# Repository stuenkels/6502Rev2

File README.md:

# 6502v2 Computer Build

Please note while this design is based on Ben Eaters 6502 (eater.net/6502) computer, it is not 100% compatible. This is mostly due to the memory map being changed to make space for 3 interface chips, 2 c22s and a c51. 

Memory Map:
  0x0000 -> 0x3FFF : RAM
  0x4010 : Start of memory for the "GPIO" VIA
  0x4020 : Start of memory for the "LCD" VIA
  0x4040 : Start of memory for the Serial interface
  0x8000 -> 0xFFFF : ROM

It is very simple to refactor any code written for the BE6502 to work with this design, all you have to do is change the definitions for the different ports, ex PORTB = $6020 would be PORTB = $4020.  

# Pictures

<br>
The LCD header was mirrored on this first run of boards, the GERBER files and KiCad project have been updated in the repo.

If you want to build this PCB yourself, you can download the gerber.zip file and order it from JLCPCB or PCBWAY
MAKE SURE TO USE A FEMALE DB9 CONNECTOR FOR THE SERIAL PORT!!! The connecture in the picture is a male connector, and it does not work because the pins are in the wrong spots!

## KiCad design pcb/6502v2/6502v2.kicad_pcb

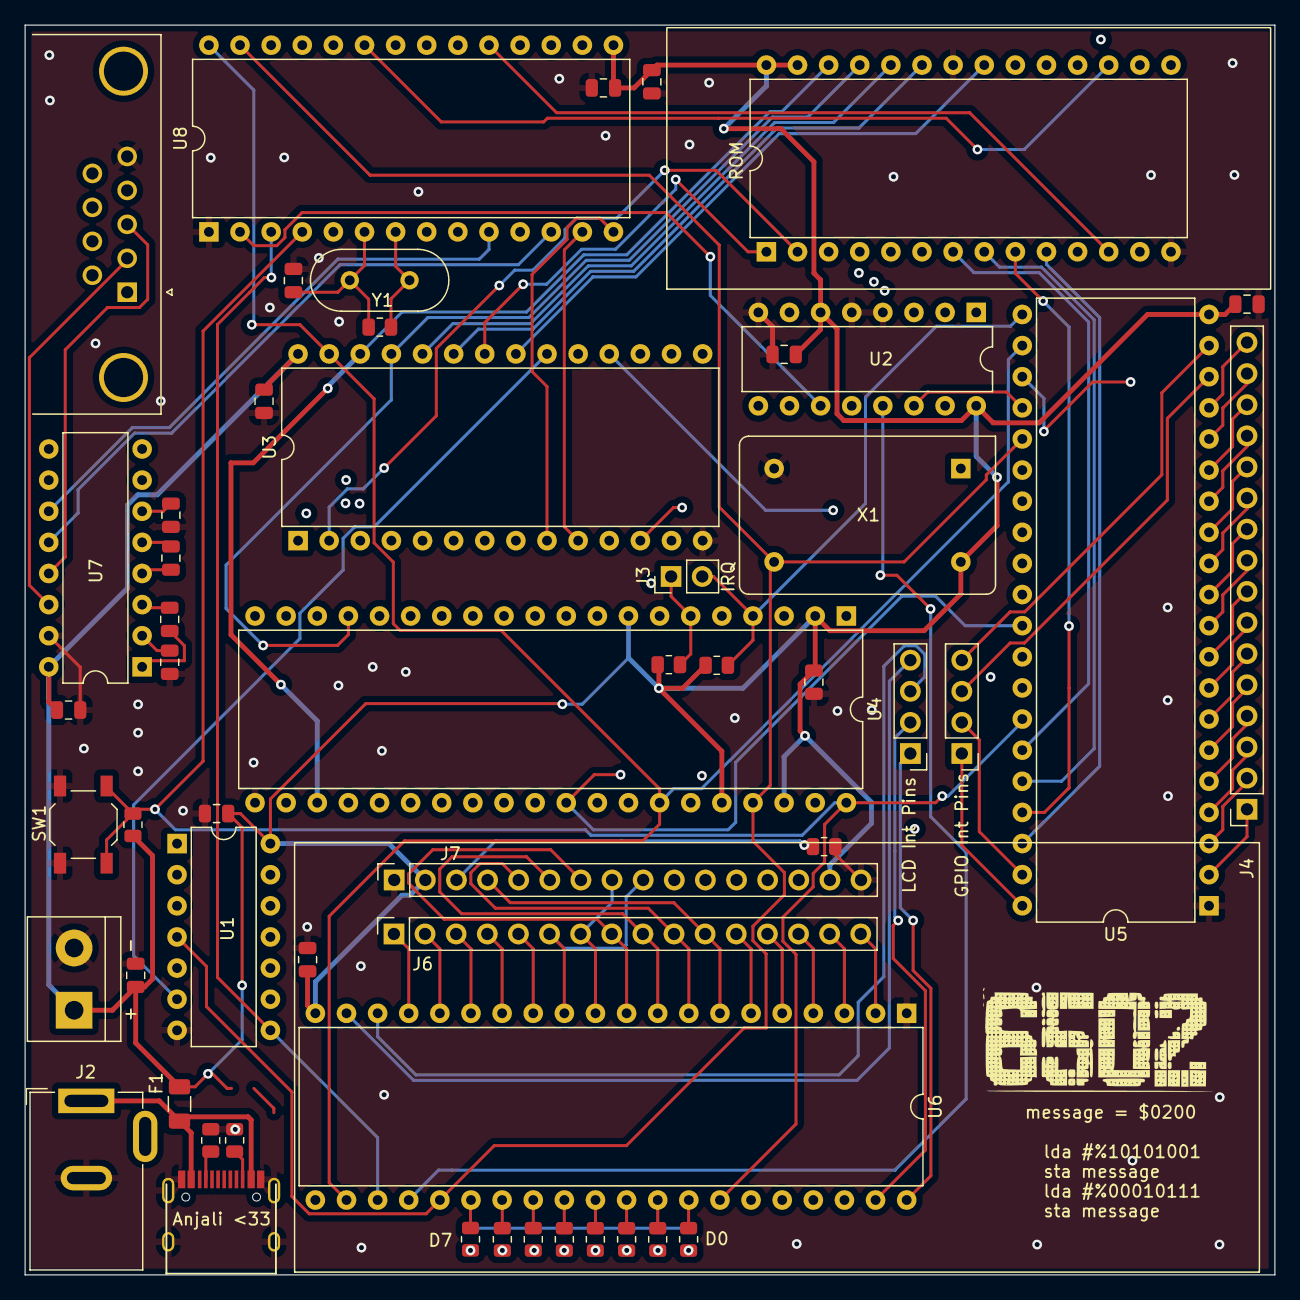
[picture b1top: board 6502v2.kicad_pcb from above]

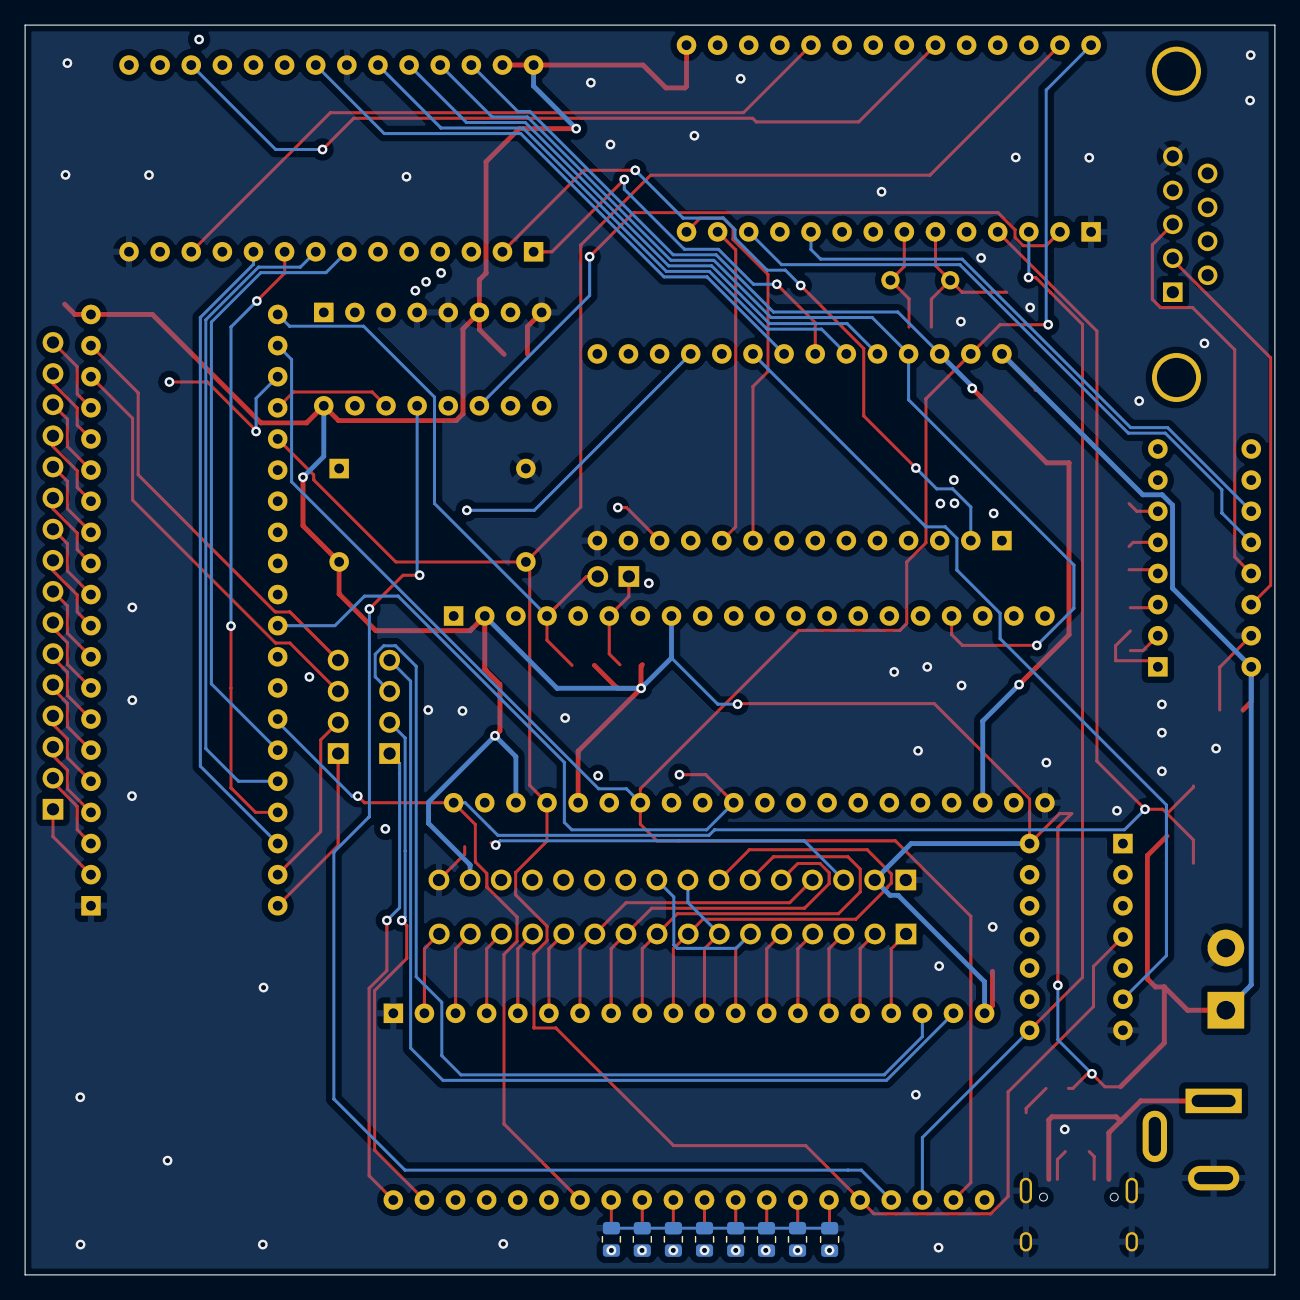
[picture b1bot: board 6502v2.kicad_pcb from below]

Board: 4 copper layers, 102.0 x 102.0 mm, 61 parts (8 on the bottom side), 101 nets.

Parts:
C1, C2, C3, C4, C5, C6, C7, C8, C9, C10: 10uF; C_0805_2012Metric
C11, C12, C13, C14: 1µF; C_0805_2012Metric
C15: 30 pF; C_0805_2012Metric
D2, D4, D6, D8, D10, D12, D14, D16: Blu; R_0805_2012Metric
F1: Polyfuse_Small; Fuse_1206_3216Metric
J1: Power; TerminalBlock_bornier-2_P5.08mm
J2: Barrel_Jack; BarrelJack_GCT_DCJ200-10-A_Horizontal
J3: Conn_01x02; PinHeader_1x02_P2.54mm_Vertical
J4, J6: I/O; PinSocket_1x16_P2.54mm_Vertical
J5, J8: Interup Pins; PinHeader_1x04_P2.54mm_Vertical
J7: LDC; PinSocket_1x16_P2.54mm_Vertical
J9: DB9_Female; DSUB-9_Female_Horizontal_P2.77x2.84mm_EdgePinOffset4.94mm_H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
R1, R2: 5.1k; R_0805_2012Metric
R4, R6, R8, R10, R12, R14, R16, R18, R29, R30: 220; R_0805_2012Metric
R31: 1k; R_0805_2012Metric
R32: R_Small; R_0805_2012Metric
R33: 1M; R_0805_2012Metric
SW1: SW_Push; SW_SPST_TL3342
U1: 74HC00; DIP-14_W7.62mm
U2: 74HC238; DIP-16_W7.62mm
U3: CY62256-70PC; DIP-28_W15.24mm
U4: W65C02SxP; DIP-40_W15.24mm
U5, U6: W65C22NxP; DIP-40_W15.24mm
U7: MAX232; DIP-16_W7.62mm
U8: W65C51NxP; DIP-28_W15.24mm
U9: 28C256; DIP-28_W15.24mm
USB1: HRO-TYPE-C-31-M-12
X1: DGOF5S3; Oscillator_DIP-14
Y1: 1.8432 Mh; Crystal_HC49-U_Vertical

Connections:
+5V: C1.1, C2.1, C3.1, C4.1, C5.1, C6.1, C7.1, C8.1, C9.1, C10.1, F1.2, J1.1, J7.2, J7.15, R29.1, R30.1, R31.1, U1.14 (VCC), U2.6 (E3), U2.16 (VCC), U3.28 (VCC), U4.2 (RDY), U4.8 (VDD), U4.36 (BE), U4.38 (~SO), U5.20 (VCC), U6.20 (VCC), U7.16 (VCC), U8.15 (VCC), U9.27 (~WE), U9.28 (VCC), X1.14 (Vcc)
/A0: U3.10 (A0), U4.9 (A0), U5.38 (RS0), U6.38 (RS0), U8.13 (RS0), U9.10 (A0)
/A1: U3.9 (A1), U4.10 (A1), U5.37 (RS1), U6.37 (RS1), U8.14 (RS1), U9.9 (A1)
/A2: U3.8 (A2), U4.11 (A2), U5.36 (RS2), U6.36 (RS2), U9.8 (A2)
/A3: U3.7 (A3), U4.12 (A3), U5.35 (RS3), U6.35 (RS3), U9.7 (A3)
/A4: U2.1 (A0), U3.6 (A4), U4.13 (A4), U9.6 (A4)
/A5: U2.2 (A1), U3.5 (A5), U4.14 (A5), U9.5 (A5)
/A6: U2.3 (A2), U3.4 (A6), U4.15 (A6), U9.4 (A6)
/A7: U3.3 (A7), U4.16 (A7), U9.3 (A7)
/A8: U3.25 (A8), U4.17 (A8), U9.25 (A8)
/A9: U3.24 (A9), U4.18 (A9), U9.24 (A9)
/A10: U3.21 (A10), U4.19 (A10), U9.21 (A10)
/A11: U3.23 (A11), U4.20 (A11), U9.23 (A11)
/A12: U3.2 (A12), U4.22 (A12), U9.2 (A12)
/A13: U3.26 (A13), U4.23 (A13), U9.26 (A13)
/A14: U1.9, U3.1 (A14), U3.22 (~OE), U4.24 (A14), U9.1 (A14)
/A15: U1.12, U1.13, U4.25 (A15)
/C22 Enable: U2.14 (Y1), U5.24 (CS1)
/CPU/NMI: J3.1, R29.2, U4.6 (~NMI)
/Clk: U1.4, U4.37 (ϕ0), U5.25 (ϕ2), U6.25 (ϕ2), U8.27 (ϕ2), X1.8 (OUT)
/D0: D2.2 (A), U3.11 (Q0), U4.33 (D0), U5.33 (D0), U6.33 (D0), U8.18 (D0), U9.11 (D0)
/D1: D4.2 (A), U3.12 (Q1), U4.32 (D1), U5.32 (D1), U6.32 (D1), U8.19 (D1), U9.12 (D1)
/D2: D6.2 (A), U3.13 (Q2), U4.31 (D2), U5.31 (D2), U6.31 (D2), U8.20 (D2), U9.13 (D2)
/D3: D8.2 (A), U3.15 (Q3), U4.30 (D3), U5.30 (D3), U6.30 (D3), U8.21 (D3), U9.15 (D3)
/D4: D10.2 (A), U3.16 (Q4), U4.29 (D4), U5.29 (D4), U6.29 (D4), U8.22 (D4), U9.16 (D4)
/D5: D12.2 (A), U3.17 (Q5), U4.28 (D5), U5.28 (D5), U6.28 (D5), U8.23 (D5), U9.17 (D5)
/D6: D14.2 (A), U3.18 (Q6), U4.27 (D6), U5.27 (D6), U6.27 (D6), U8.24 (D6), U9.18 (D6)
/D7: D16.2 (A), U3.19 (Q7), U4.26 (D7), U5.26 (D7), U6.26 (D7), U8.25 (D7), U9.19 (D7)
/IRQ: J3.2, R30.2, U4.4 (~IRQ), U5.21 (~IRQ)
/I/O ~Enable: U1.8, U5.23 (~CS2), U6.23 (~CS2), U8.3 (~CS2)
/LCD C22 Enable: U2.13 (Y2), U6.24 (CS1)
/RAM ~CS: U1.6, U3.20 (~CS)
/Reset: R31.2, SW1.2, U4.40 (~RES), U5.34 (~RES), U6.34 (~RES), U8.4 (~RES)
/R/W: U3.27 (~WE), U4.34 (R/~W), U5.22 (R/~W), U6.22 (R/~W), U8.28 (R/~W)
/Serial Enable: U2.11 (Y4), U8.2 (CS1)
/Serial/R1IN: J9.3, U7.13 (R1IN)
/Serial/R1OUT: U7.12 (R1OUT), U8.12 (RxD)
/Serial/T1IN: U7.11 (T1IN), U8.10 (TxD)
/Serial/T1OUT: J9.2, U7.14 (T1OUT)
/VIA/CA1: J5.1, U5.40 (CA1)
/VIA/CA2: J5.2, U5.39 (CA2)
/VIA/CB1: J5.3, U5.18 (CB1)
/VIA/CB2: J5.4, U5.19 (CB2)
/VIA/LCD CA1: J8.1, U6.40 (CA1)
/VIA/LCD CA2: J8.2, U6.39 (CA2)
/VIA/LCD CB1: J8.3, U6.18 (CB1)
/VIA/LCD CB2: J8.4, U6.19 (CB2)
/VIA/LCD PA0: J6.16, U6.2 (PA0)
/VIA/LCD PA1: J6.15, U6.3 (PA1)
/VIA/LCD PA2: J6.14, U6.4 (PA2)
/VIA/LCD PA3: J6.13, U6.5 (PA3)
/VIA/LCD PA4: J6.12, U6.6 (PA4)
/VIA/LCD PA5: J6.11, J7.4, U6.7 (PA5)
/VIA/LCD PA6: J6.10, J7.5, U6.8 (PA6)
/VIA/LCD PA7: J6.9, J7.6, U6.9 (PA7)
/VIA/LCD PB0: J6.8, J7.7, U6.10 (PB0)
/VIA/LCD PB1: J6.7, J7.8, U6.11 (PB1)
/VIA/LCD PB2: J6.6, J7.9, U6.12 (PB2)
/VIA/LCD PB3: J6.5, J7.10, U6.13 (PB3)
/VIA/LCD PB4: J6.4, J7.11, U6.14 (PB4)
/VIA/LCD PB5: J6.3, J7.12, U6.15 (PB5)
/VIA/LCD PB6: J6.2, J7.13, U6.16 (PB6)
/VIA/LCD PB7: J6.1, J7.14, U6.17 (PB7)
/VIA/PA0: J4.1, U5.2 (PA0)
/VIA/PA1: J4.2, U5.3 (PA1)
/VIA/PA2: J4.3, U5.4 (PA2)
/VIA/PA3: J4.4, U5.5 (PA3)
/VIA/PA4: J4.5, U5.6 (PA4)
/VIA/PA5: J4.6, U5.7 (PA5)
/VIA/PA6: J4.7, U5.8 (PA6)
/VIA/PA7: J4.8, U5.9 (PA7)
/VIA/PB0: J4.9, U5.10 (PB0)
/VIA/PB1: J4.10, U5.11 (PB1)
/VIA/PB2: J4.11, U5.12 (PB2)
/VIA/PB3: J4.12, U5.13 (PB3)
/VIA/PB4: J4.13, U5.14 (PB4)
/VIA/PB5: J4.14, U5.15 (PB5)
/VIA/PB6: J4.15, U5.16 (PB6)
/VIA/PB7: J4.16, U5.17 (PB7)
/~A15: U1.5, U1.10, U1.11, U9.20 (~CS)
GND: C1.2, C2.2, C3.2, C4.2, C5.2, C6.2, C7.2, C8.2, C9.2, C10.2, C13.2, C14.2, C15.2, J1.2, J2.2, J7.1, J7.16, J9.5, R1.2, R2.2, R4.2, R6.2, R8.2, R10.2, R12.2, R14.2, R16.2, R18.2, R32.2, SW1.1, U1.7 (GND), U2.4 (~E1), U2.5 (~E2), U2.8 (GND), U3.14 (GND), U4.21 (VSS), U5.1 (VSS), U6.1 (VSS), U7.15 (GND), U8.1 (VSS), U9.14 (GND), U9.22 (~OE), USB1.1 (GND), USB1.12 (GND), USB1.13 (SHIELD), X1.7 (GND)
unnamed: C11.1, U7.1 (C1+)
unnamed: C11.2, U7.3 (C1-)
unnamed: C12.1, U7.4 (C2+)
unnamed: C12.2, U7.5 (C2-)
unnamed: C13.1, U7.6 (VS-)
unnamed: C14.1, U7.2 (VS+)
unnamed: C15.1, R33.1, U8.6 (XTAL1), Y1.2
unnamed: D2.1 (K), R4.1
unnamed: D4.1 (K), R6.1
unnamed: D6.1 (K), R8.1
unnamed: D8.1 (K), R10.1
unnamed: D10.1 (K), R12.1
unnamed: D12.1 (K), R14.1
unnamed: D14.1 (K), R16.1
unnamed: D16.1 (K), R18.1
unnamed: J7.3, R32.1
unnamed: R1.1, USB1.4 (CC1)
unnamed: R2.1, USB1.10 (CC2)
unnamed: R33.2, U8.7 (XTAL2), Y1.1
VCC: F1.1, J2.1, USB1.2 (VBUS), USB1.11 (VBUS)

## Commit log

2023-06-23 added readme
2023-06-23 Change filenames
2023-06-23 fles change
2023-06-23 Update schematic
2023-06-30 Changed stufffs
2023-06-30 UART more like u r dumb
2023-07-01 Finally figured out the address decode logic, hopefully im done for now
2023-07-02 just working
2023-07-02 Laying out chips
2023-07-03 Yo yo yo i make the bord 102 by 102 cause jlc pricing
2023-07-04 First pass at routing done, now comes double checking everything
2023-07-04 Tidying up schematic
2023-07-04 Oh\?\!\?\!\? Is that a gerber i see\?\!\?\!
2023-07-04 Ok i rembered to generate drill files this time
2023-07-04 Finishing up
2023-07-04 Typo fix
2023-07-05 Removed burried VIAs because jlc cant produce them
2023-08-05 Fixed mirrored footprints, updated readme
2023-08-05 readme fix
2023-08-05 readme
2023-08-10 Import Readme fix
